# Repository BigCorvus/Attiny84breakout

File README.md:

# Attiny84breakout
Small breakout board for the Attiny84 in a QFN package

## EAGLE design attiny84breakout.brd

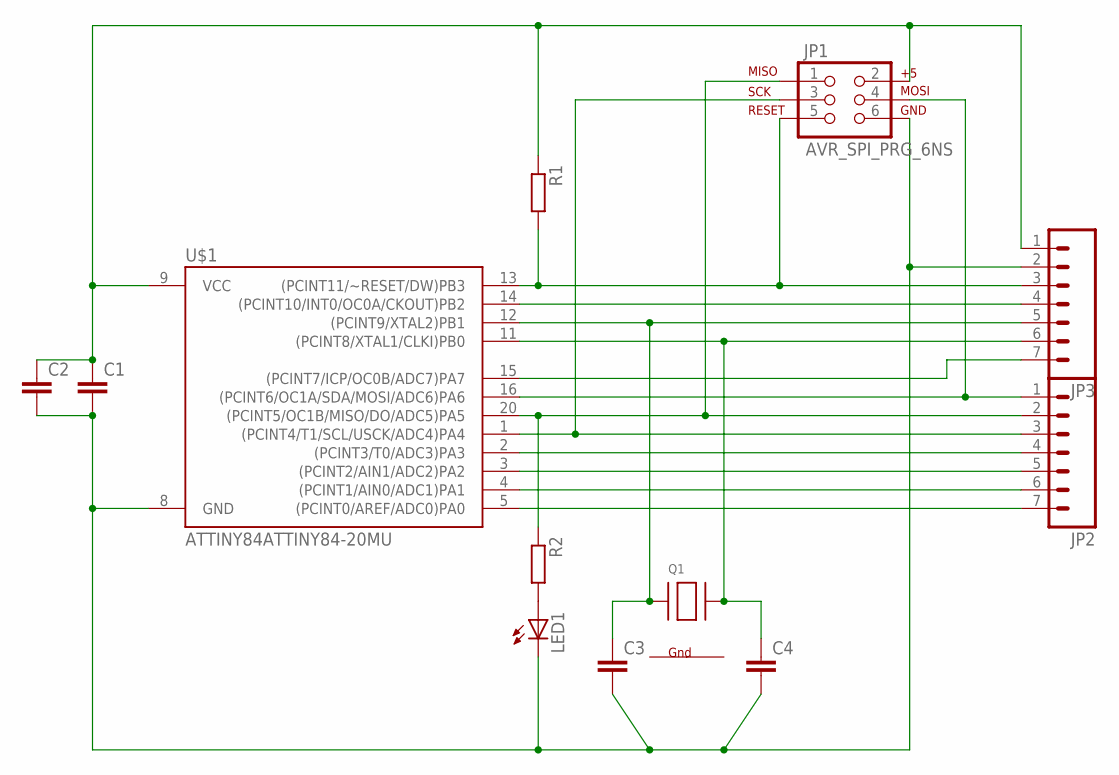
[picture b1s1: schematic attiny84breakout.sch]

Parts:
C1, C2, C3, C4: C-EUC0402; C0402
JP1: AVR_SPI_PRG_6NS; 2X3-NS
JP2, JP3: M07; 1X07
LED1: LEDCHIP-LED0805; CHIP-LED0805
Q1: XTAL-4-3225; NX3225
R1, R2: R-EU_R0603; R0603
U$1: ATTINY84ATTINY84-20MU; QFN20

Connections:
G1: Q1.4 (G1)
G2: Q1.2 (G2)
GND: C1.2, C2.2, C3.2, C4.2, JP1.6, JP3.2, LED1.C, U$1.8 (GND)
unnamed: JP2.7, U$1.5 ((PCINT0/AREF/ADC0)PA0)
unnamed: JP2.6, U$1.4 ((PCINT1/AIN0/ADC1)PA1)
unnamed: JP1.5, JP3.3, R1.2, U$1.13 ((PCINT11/~RESET/DW)PB3)
unnamed: JP1.3, JP2.3, U$1.1 ((PCINT4/T1/SCL/USCK/ADC4)PA4)
unnamed: JP1.4, JP2.1, U$1.16 ((PCINT6/OC1A/SDA/MOSI/ADC6)PA6)
unnamed: JP1.1, JP2.2, R2.1, U$1.20 ((PCINT5/OC1B/MISO/DO/ADC5)PA5)
unnamed: C1.1, C2.1, JP1.2, JP3.1, R1.1, U$1.9 (VCC)
unnamed: LED1.A, R2.2
unnamed: JP2.5, U$1.3 ((PCINT2/AIN1/ADC2)PA2)
unnamed: JP2.4, U$1.2 ((PCINT3/T0/ADC3)PA3)
unnamed: JP3.7, U$1.15 ((PCINT7/ICP/OC0B/ADC7)PA7)
unnamed: C3.1, JP3.5, Q1.1 (X1), U$1.12 ((PCINT9/XTAL2)PB1)
unnamed: JP3.4, U$1.14 ((PCINT10/INT0/OC0A/CKOUT)PB2)
unnamed: C4.1, JP3.6, Q1.3 (X2), U$1.11 ((PCINT8/XTAL1/CLKI)PB0)

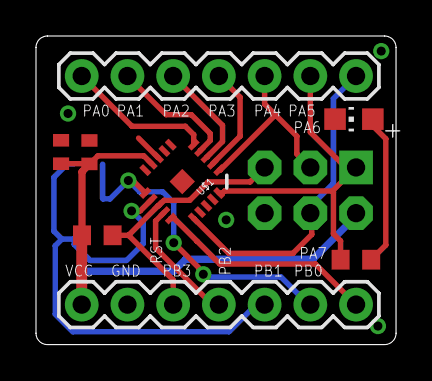
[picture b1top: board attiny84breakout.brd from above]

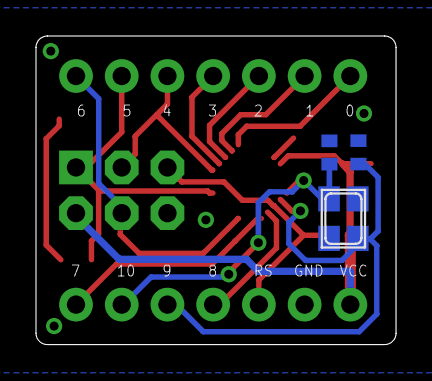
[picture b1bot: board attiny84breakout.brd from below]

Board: 2 copper layers, 20.0 x 17.1 mm, 12 parts (3 on the bottom side), 15 nets.

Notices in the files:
parts and their libraries:
SparkFun-Connectors: Licensing: Creative Commons ShareAlike 4.0 International - https://creativecommons.org/licenses/by-sa/4.0
